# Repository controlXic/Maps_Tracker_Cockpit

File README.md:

# Control Xic Maps

## Overview

The goal of this research project was to develop a motorcycle-mounted navigation device capable of displaying offline vector maps, recording GPS tracks, and providing navigation capabilities.
 
## Project Background

The first prototype was based on an STM32H743 microcontroller paired with a 5-inch display. It used raster map tiles (`tiles.png`), but map rendering and processing performance proved to be too slow.

We then explored switching to vector maps. However, the learning curve and complexity of the available libraries made this approach challenging with the STM32 platform.

Eventually, we decided to move to a microprocessor-based platform — or, to put it simply, the easier option\!

One might ask: why not simply use an Android application, considering that excellent alternatives such as DMD2 already exist?

Well, because this device is fully integrated into the motorcycle — And, most importantly, it’s my pastime!\!

## App Features

- **Offline maps:** The app uses `maps.osm.pbf` files converted into the `MBTiles` format using Tilemaker.
- **Automatic track recording:** When the motorcycle is started, the device automatically begins recording a GPS track. The recorded track can later be saved or discarded, ensuring that no recording is lost unintentionally.
- **Multiple tracks:** Several GPX tracks can be loaded and displayed simultaneously.
- **Map display options:** Various map overlays and display settings are available, including gas stations, town names, mountain peaks, and night mode.
- **GPX Server:** Enabling the **GPX SERVER** switch creates a Wi-Fi access point and makes a web interface available through a local IP address. This allows tracks to be uploaded or downloaded and application updates to be installed.
- **Custom map generation:** Maps can be generated for individual countries or multiple countries combined, using Tilemaker.

## Power Management and Vehicle Integration

The device is fully integrated into the motorcycle's electrical system and uses the **KL30 (permanent battery supply)** and the **ignition switch** to manage its power state.

It is powered directly from the motorcycle's battery and uses a MOSFET-based power management circuit to completely disconnect the device when the motorcycle is stationary, ensuring zero standby power consumption.

Startup and shutdown are therefore fully synchronized with the motorcycle and handled automatically.

The power management logic works as follows:

- **Power-on:** The device starts when power is detected on the KL30 line.
- **Push-button shutdown:** If the device is switched off using the motorbike off-push-button, shutdown is delayed by 5 minutes.
- **Ignition shutdown:** When the ignition is switched off, the device shuts down immediately.

## Hardware

The device is built around an **Orange Pi Zero 2 W(4 GB RAM)**, a compact board offering a good balance between performance and size.

Main hardware components:

- **Main board:** Orange Pi Zero 2 W(4 GB RAM).
- **Display:** Waveshare 5-inch, 1280 × 720 touchscreen.
- **GPS:** Integrated GPS NEO-8M module with an external antenna.
- **Custom PCB:** Designed specifically to integrate and connect all the hardware components.

### Custom PCB Connections

The custom PCB includes a dedicated connector for the motorcycle electrical system and external peripherals.

The connector provides the following signals:

| Signal | Description |
| --- | --- |
| KL30 | Set when Motor i on |
| Key | key switch signal |
| VBAT + GND | Battery power and ground |
| GPS antenna + GND | External GPS antenna connection |
| 5V + GND | Power supply for the handlebar-mounted Bluetooth controller (comming soon)|

## Software

The software is developed using **Qt** and **QGIS libraries**, providing the mapping and navigation functionality.

## Images

Device    

App Tabs and GPX SERVER web   

## Additional Notes

The original hardware design also included an IMU (Inertial Measurement Unit).

The IMU-related code is still present in the project but has been commented out. It was initially intended to support additional features such as:

- ADAS (Advanced Driver Assistance Systems).
- HD Vehicle speed monitoring.
- Motion and sensor data logging.

These features were ultimately dropped and are not part of the current implementation.

Thanks to @qgis for its open-source libraries, as the project would not have been possible without them.

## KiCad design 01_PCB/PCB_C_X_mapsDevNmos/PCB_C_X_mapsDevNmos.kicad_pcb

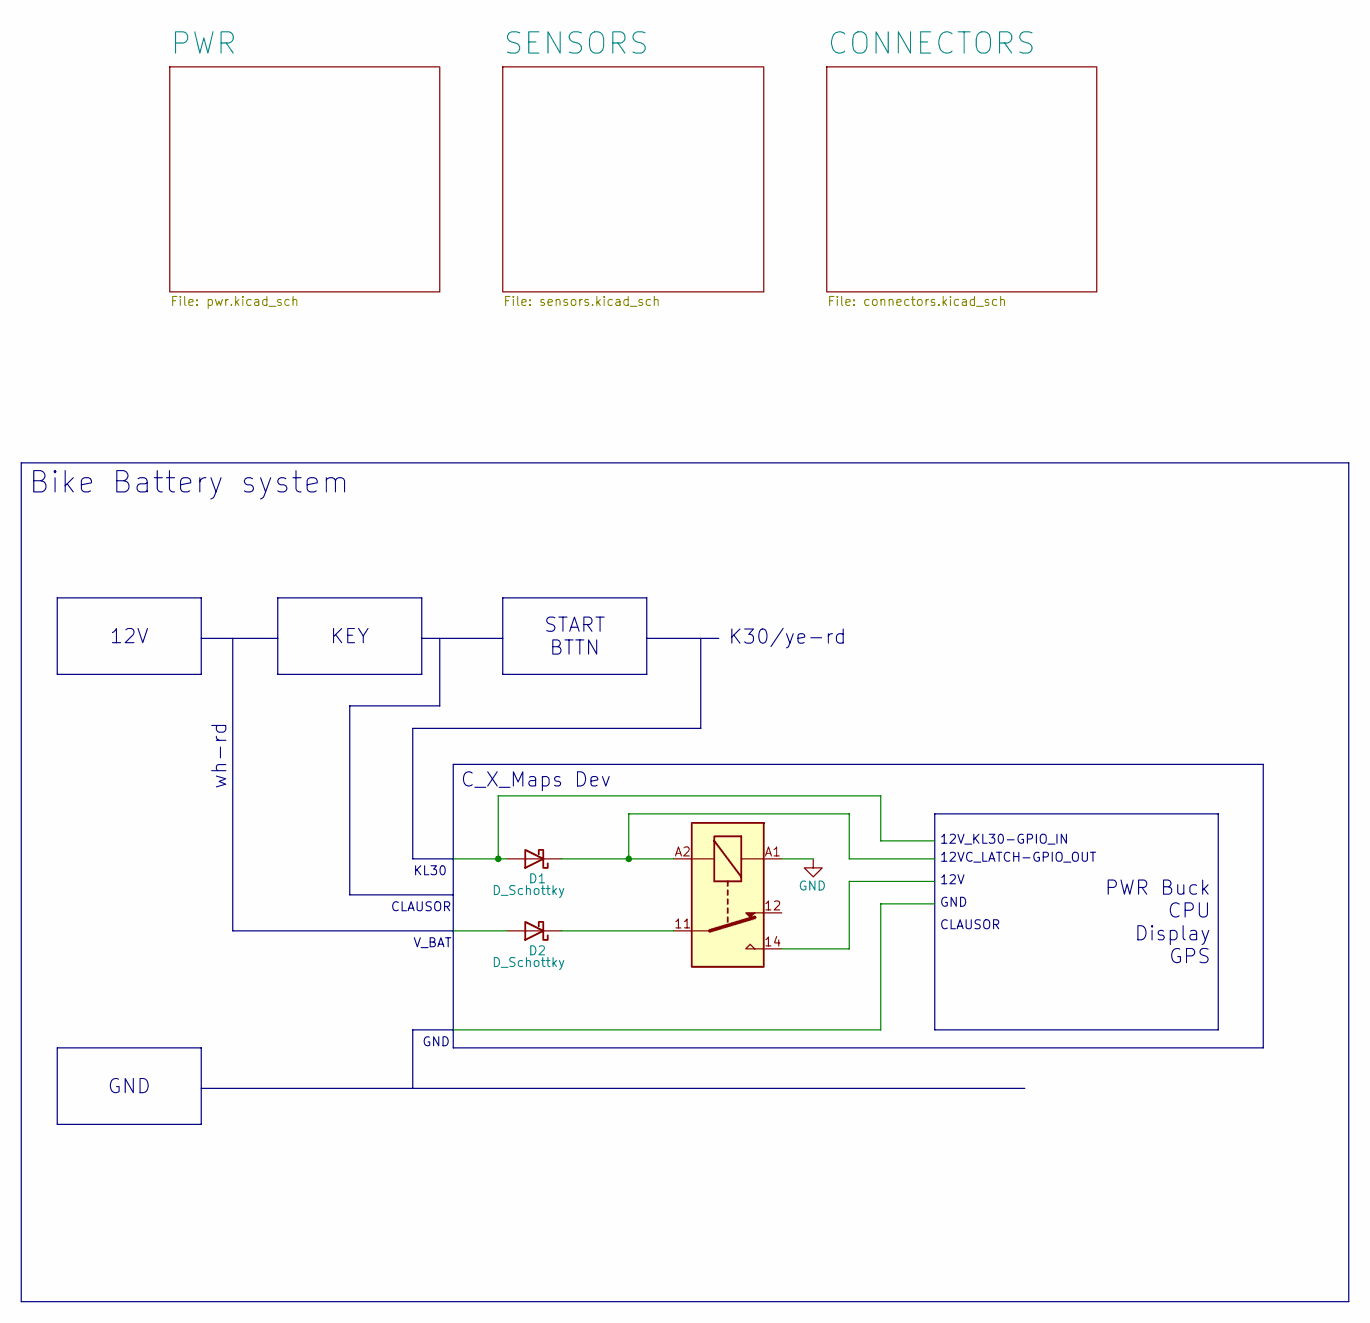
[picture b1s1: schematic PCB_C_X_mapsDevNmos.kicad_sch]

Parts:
D1, D2: D_Schottky; Vishay_SMPA
K1: Fujitsu_FTR-LYCA005x; Relay_SPDT_Fujitsu_FTR-LYCA005x_FormC_Vertical

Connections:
unnamed: D1.1 (K), K1.A2
unnamed: D2.1 (K), K1.11

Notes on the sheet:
CLAUSOR
12VC_LATCH-GPIO_OUT
V_BAT
GND
KL30
12V
wh-rd
K30/ye-rd
12V_KL30-GPIO_IN
START BTTN
Bike Battery system
PWR Buck CPU Display GPS
KEY
C_X_Maps Dev

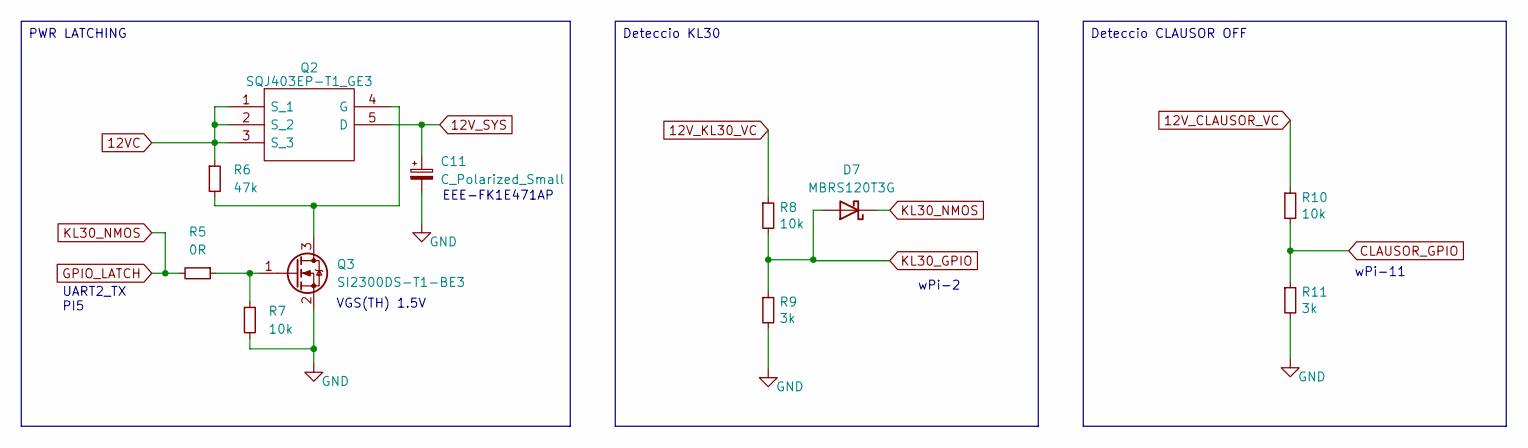
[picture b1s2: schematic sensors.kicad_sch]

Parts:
C11: C_Polarized_Small; CP_Elec_10x10.5
D7: MBRS120T3G; D_SMB
Q2: SQJ403EP-T1_GE3; SQJA72EPT1_GE3; Manufacturer_Part_Number SQJ481EP-T1_GE3; Mouser Part Number 78-SQJ481EP-T1_GE3
Q3: SI2300DS-T1-BE3; SOT-23
R5: 0R; R_0603_1608Metric
R6: 47k; R_0603_1608Metric
R7, R8, R10: 10k; R_0603_1608Metric
R9, R11: 3k; R_0603_1608Metric

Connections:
12VC: Q2.1 (S_1), Q2.2 (S_2), Q2.3 (S_3), R6.1; also elsewhere on the board
12V_CLAUSOR_VC: R10.1; also elsewhere on the board
12V_KL30_VC: R8.1; also elsewhere on the board
12V_SYS: C11.1, Q2.5 (D); also elsewhere on the board
CLAUSOR_GPIO: R10.2, R11.1; also elsewhere on the board
GND: C11.2, Q3.2 (S), R7.2, R9.2, R11.2; also elsewhere on the board
GPIO_LATCH: D7.1 (K), R5.2; also elsewhere on the board
KL30_GPIO: D7.2 (A), R8.2, R9.1; also elsewhere on the board
unnamed: Q2.4 (G), Q3.3 (D), R6.2
unnamed: Q3.1 (G), R5.1, R7.1

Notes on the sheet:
VGS(TH) 1.5V
wPi-11
EEE-FK1E471AP
wPi-2
UART2_TX PI5
Deteccio CLAUSOR OFF
Deteccio KL30
PWR LATCHING

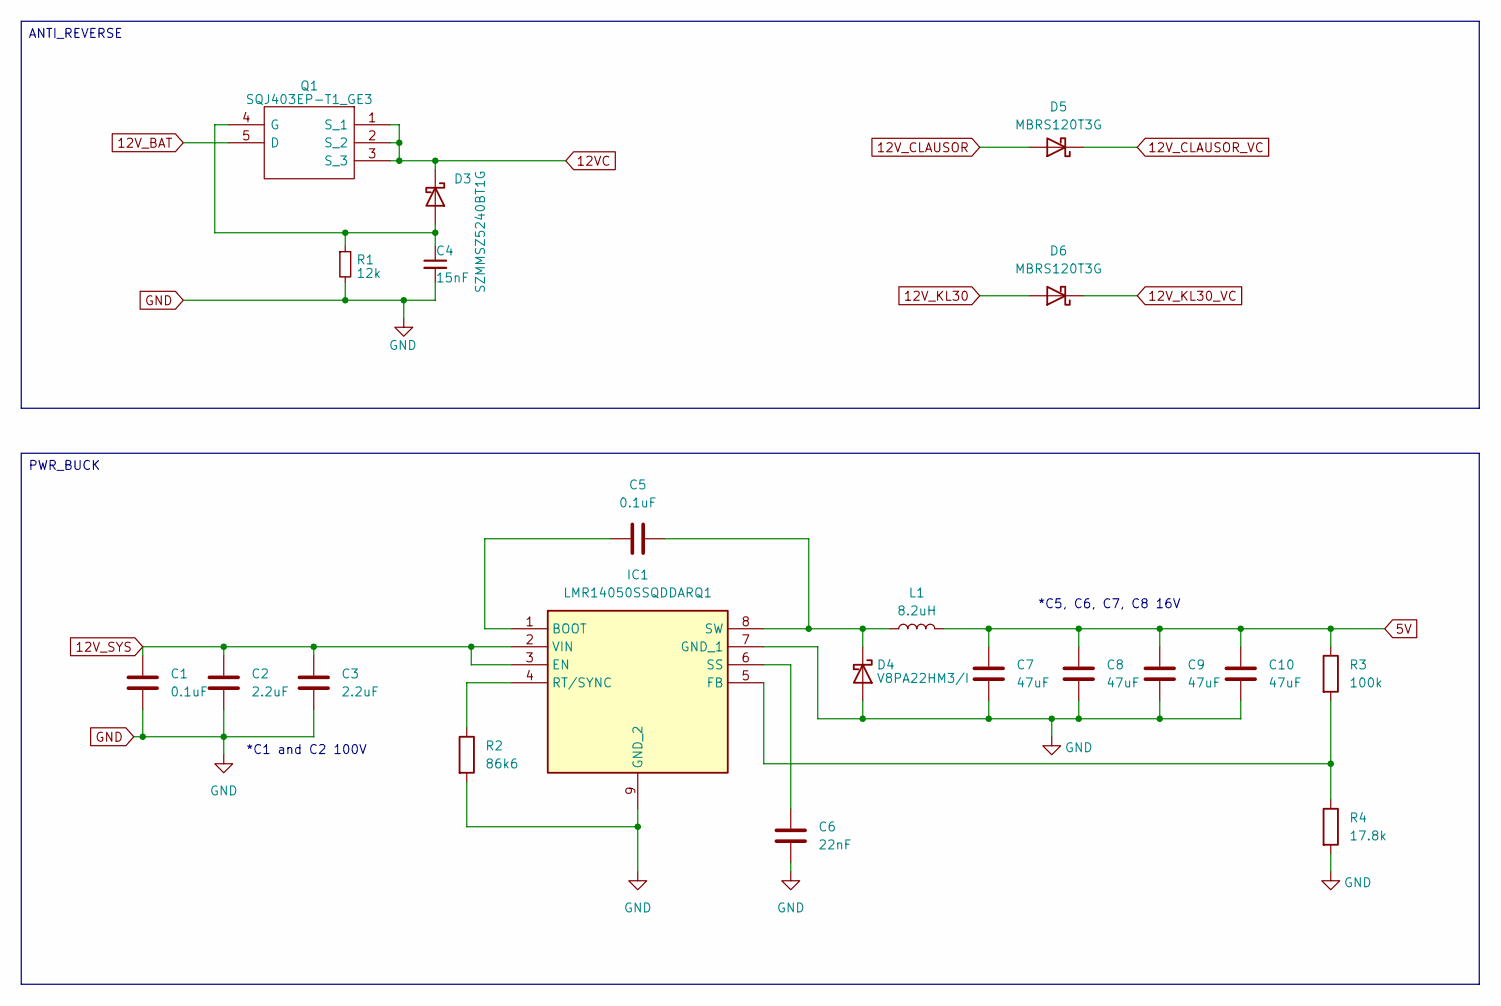
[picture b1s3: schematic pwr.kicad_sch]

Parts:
C1, C5: 0.1uF; C_0805_2012Metric_Pad1.18x1.45mm_HandSolder
C2, C3: 2.2uF; C_1210_3225Metric_Pad1.33x2.70mm_HandSolder
C4: 15nF; C_0603_1608Metric
C6: 22nF; C_0805_2012Metric_Pad1.18x1.45mm_HandSolder
C7, C8, C9, C10: 47uF; C_1210_3225Metric_Pad1.33x2.70mm_HandSolder
D3: SZMMSZ5240BT1G; D_SOD-123
D4: V8PA22HM3/I; Vishay_SMPA
D5, D6: MBRS120T3G; D_SMB
IC1: LMR14050SSQDDARQ1; SOIC127P600X170-9N; Mouser Part Number 595-LMR14050SSDDARQ1
L1: 8.2uH; L_APV_APH0850
Q1: SQJ403EP-T1_GE3; SQJA72EPT1_GE3; Manufacturer_Part_Number SQJ481EP-T1_GE3; Mouser Part Number 78-SQJ481EP-T1_GE3
R1: 12k; R_0805_2012Metric
R2: 86k6; R_0805_2012Metric_Pad1.20x1.40mm_HandSolder
R3: 100k; R_0805_2012Metric_Pad1.20x1.40mm_HandSolder
R4: 17.8k; R_0805_2012Metric_Pad1.20x1.40mm_HandSolder

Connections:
5V: C7.1, C8.1, C9.1, C10.1, L1.2, R3.1; also elsewhere on the board
12VC: D3.1 (K), Q1.1 (S_1), Q1.2 (S_2), Q1.3 (S_3); also elsewhere on the board
12V_BAT: Q1.5 (D); also elsewhere on the board
12V_CLAUSOR: D5.2 (A); also elsewhere on the board
12V_CLAUSOR_VC: D5.1 (K); also elsewhere on the board
12V_KL30: D6.2 (A); also elsewhere on the board
12V_KL30_VC: D6.1 (K); also elsewhere on the board
12V_SYS: C1.1, C2.1, C3.1, IC1.2 (VIN), IC1.3 (EN); also elsewhere on the board
GND: C1.2, C2.2, C3.2, C4.2, C6.2, C7.2, C8.2, C9.2, C10.2, D4.2 (A), IC1.7 (GND_1), IC1.9 (GND_2), R1.2, R2.2, R4.2; also elsewhere on the board
unnamed: C4.1, D3.2 (A), Q1.4 (G), R1.1
unnamed: C5.1, D4.1 (K), IC1.8 (SW), L1.1
unnamed: C5.2, IC1.1 (BOOT)
unnamed: IC1.5 (FB), R3.2, R4.1
unnamed: IC1.4 (RT/SYNC), R2.1
unnamed: C6.1, IC1.6 (SS)

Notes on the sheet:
*C1 and C2 100V
*C5, C6, C7, C8 16V
ANTI_REVERSE
PWR_BUCK

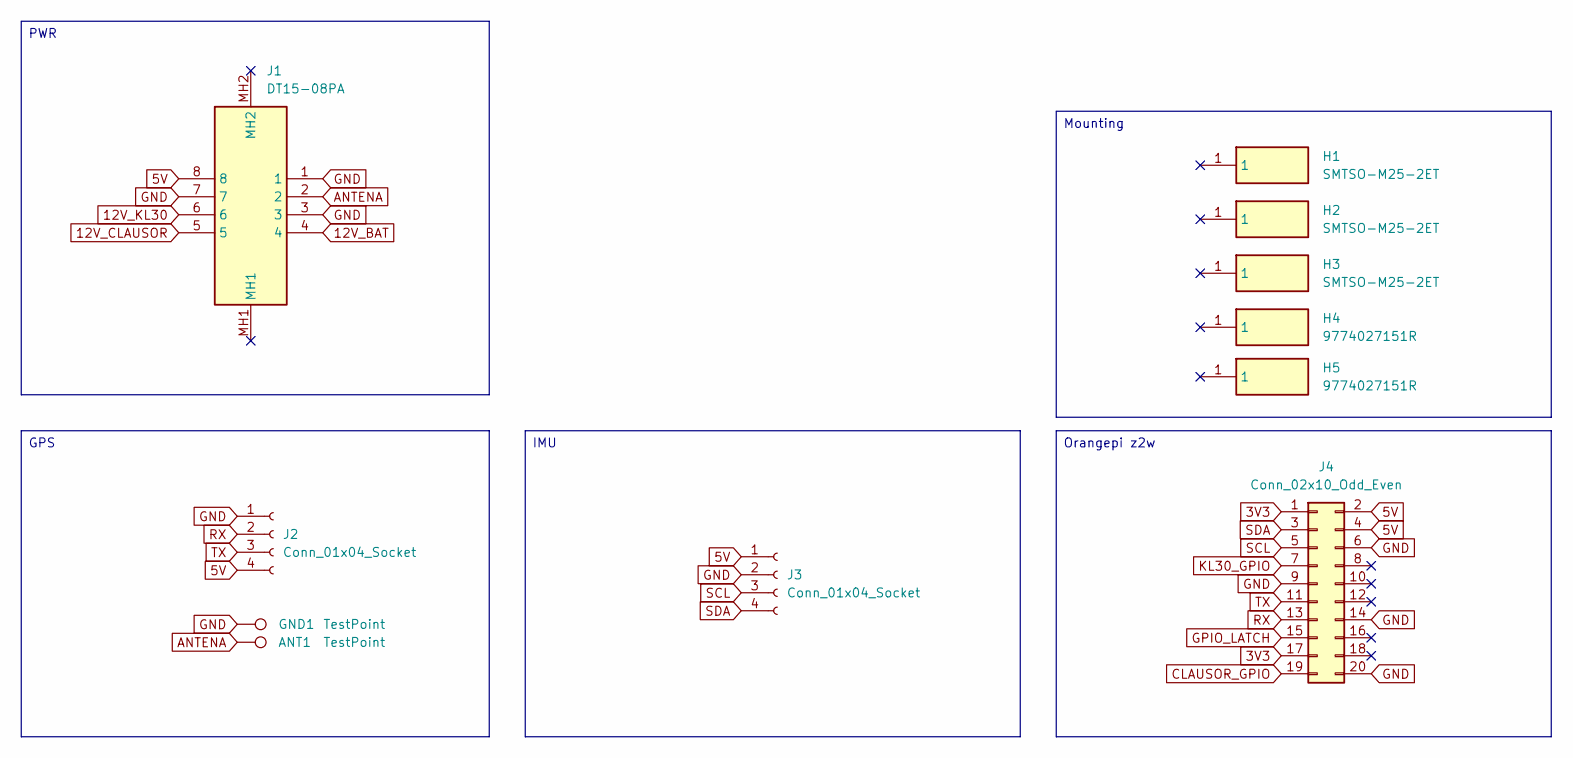
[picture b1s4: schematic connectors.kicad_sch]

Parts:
ANT1: TestPoint; TestPoint_Pad_3.0x3.0mm
GND1: TestPoint; TestPoint_Pad_3.0x3.0mm
H1, H2, H3: SMTSO-M25-2ET; SMTSOM252ET; Manufacturer_Part_Number SMTSO-M25-2ET; Mouser Part Number 153-SMTSO-M25-2ET
H4, H5: 9774027151R; Manufacturer_Part_Number 9774027151R; Mouser Part Number 710-9774027151R
J1: DT15-08PA; DT1508PA; Manufacturer_Part_Number DT15-08PA
J2, J3: Conn_01x04_Socket; PinHeader_1x04_P2.54mm_Vertical
J4: Conn_02x10_Odd_Even; PinHeader_2x10_P2.54mm_Vertical

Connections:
3V3: J4.1, J4.17
5V: J1.8, J2.4, J3.1, J4.2, J4.4; also elsewhere on the board
12V_BAT: J1.4; also elsewhere on the board
12V_CLAUSOR: J1.5; also elsewhere on the board
12V_KL30: J1.6; also elsewhere on the board
ANTENA: ANT1.1, J1.2
CLAUSOR_GPIO: J4.19; also elsewhere on the board
GND: GND1.1, J1.1, J1.3, J1.7, J2.1, J3.2, J4.6, J4.9, J4.14, J4.20; also elsewhere on the board
GPIO_LATCH: J4.15; also elsewhere on the board
KL30_GPIO: J4.7; also elsewhere on the board
RX: J2.2, J4.13
SCL: J3.3, J4.5
SDA: J3.4, J4.3
TX: J2.3, J4.11

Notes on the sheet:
Mounting
IMU
Orangepi z2w
PWR
GPS

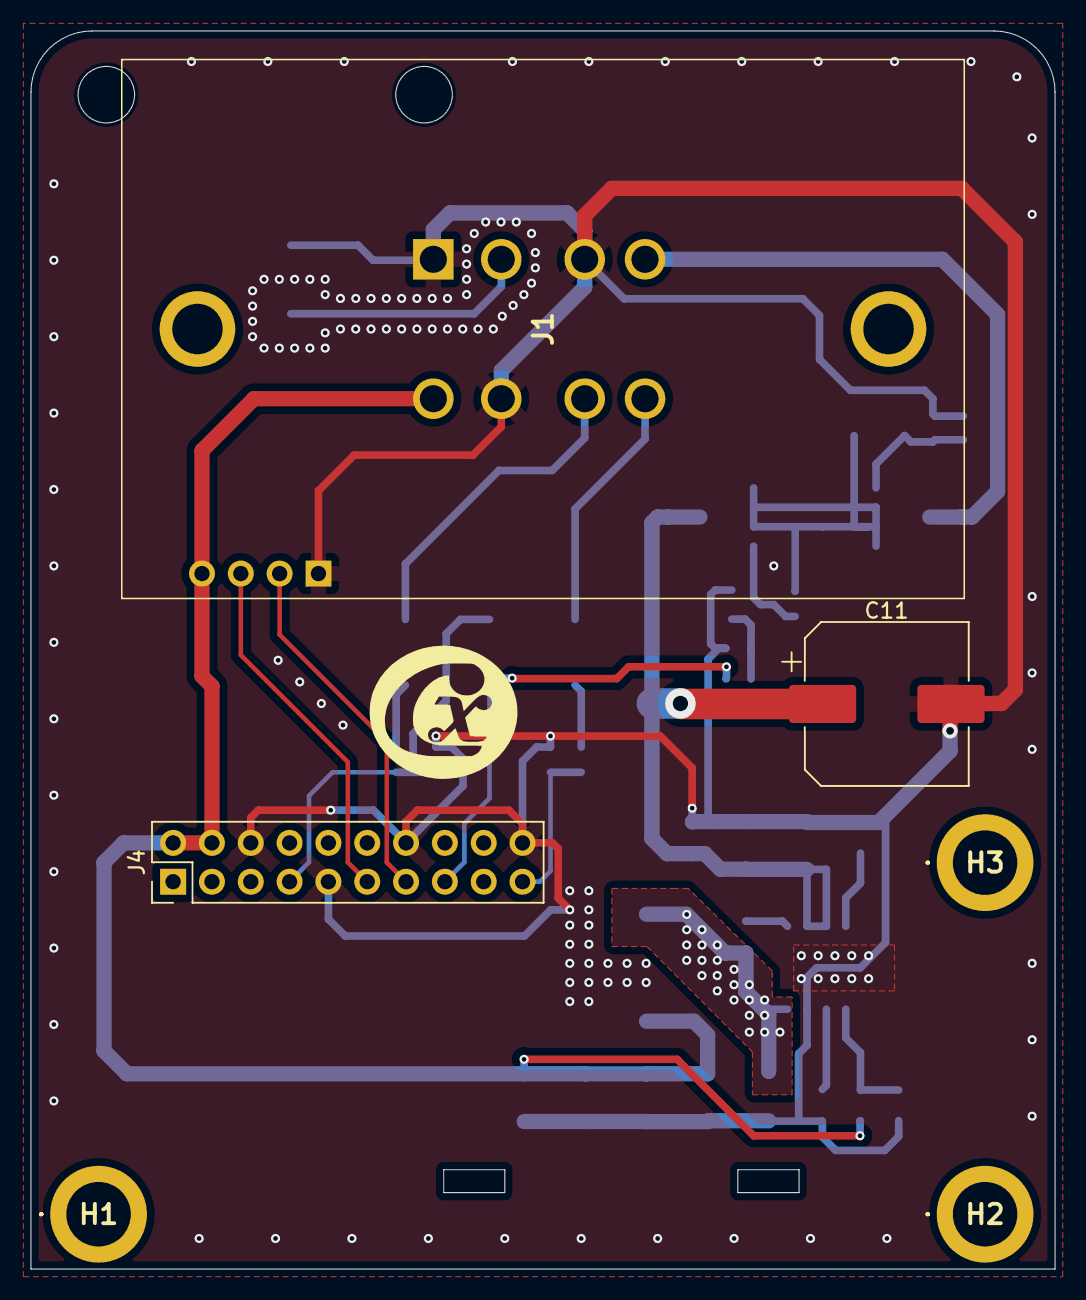
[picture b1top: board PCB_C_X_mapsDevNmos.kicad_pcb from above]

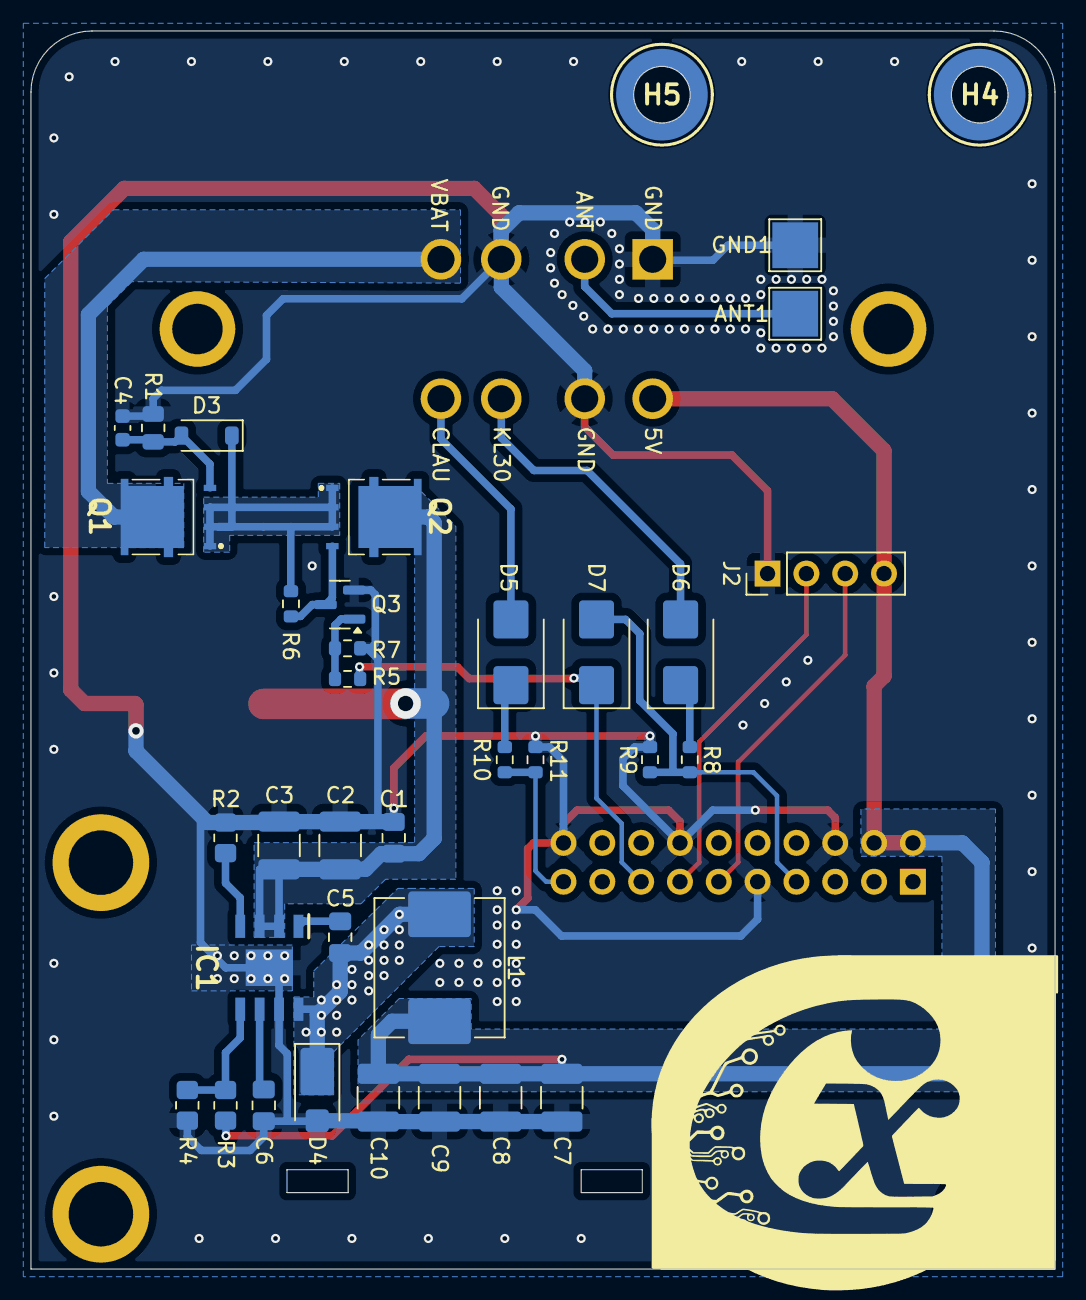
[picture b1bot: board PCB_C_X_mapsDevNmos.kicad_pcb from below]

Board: 2 copper layers, 67.0 x 81.0 mm, 42 parts (36 on the bottom side), 24 nets.
